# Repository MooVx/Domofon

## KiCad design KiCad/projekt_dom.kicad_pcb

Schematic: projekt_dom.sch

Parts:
C1: 33u; CP_Tantalum_Case-D_EIA-7343-31_Hand
C2, C3: 10u; C_0805_HandSoldering
C4: 470n; C_0805_HandSoldering
D1: IP_GOOD; LED_0805
D2: OPEN; LED_0805
J1: +12V; SolderWirePad_single_SMD_5x10mm
J2: RX; SolderWirePad_single_SMD_5x10mm
J3: OUT; SolderWirePad_single_SMD_5x10mm
J4: TX; SolderWirePad_single_SMD_5x10mm
J5: GND; SolderWirePad_single_SMD_5x10mm
Q1: NPN; SOT-23_Handsoldering
Q2: PNP; SOT-23_Handsoldering
R1, R2, R6: 1k; R_0805_HandSoldering
R3, R10: 10k; R_0805_HandSoldering
R4, R5: 100R; R_0805_HandSoldering
R7: 22k; R_0805_HandSoldering
R8: 33k; R_0805_HandSoldering
R9: 470R; R_0805_HandSoldering
U1: AMS1117-3.3; SOT-223
U2: ESP8266-12E/ESP-12E; XCVR_ESP8266-12E%2fESP-12E

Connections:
+3.3V: C1.1, C2.1, C3.1, C4.1, R1.2, R2.2, R3.2, U1.2, U2.8 (VCC)
+12V: J1.1, Q2.2, R7.2, U1.3
GND: C1.2, C2.2, C3.2, C4.2, D1.1, D2.1, J5.1, Q1.2, R10.1, U1.1, U1.4, U2.15 (GND)
unnamed: D1.2, R4.2
unnamed: D2.2, R5.1
unnamed: J2.1, U2.21 (RXD)
unnamed: J3.1, R9.1
unnamed: J4.1, U2.22 (TXD)
unnamed: Q1.1, R6.2
unnamed: Q1.3, R8.1
unnamed: Q2.1, R7.1, R8.2
unnamed: Q2.3, R9.2
unnamed: R1.1, U2.1 (RESET)
unnamed: R2.1, U2.3 (EN)
unnamed: R3.1, U2.18 (IO0)
unnamed: R4.1, U2.11 (IO9)
unnamed: R10.2, U2.16 (IO15)
OPEN: R5.2, R6.1, U2.6 (IO12)

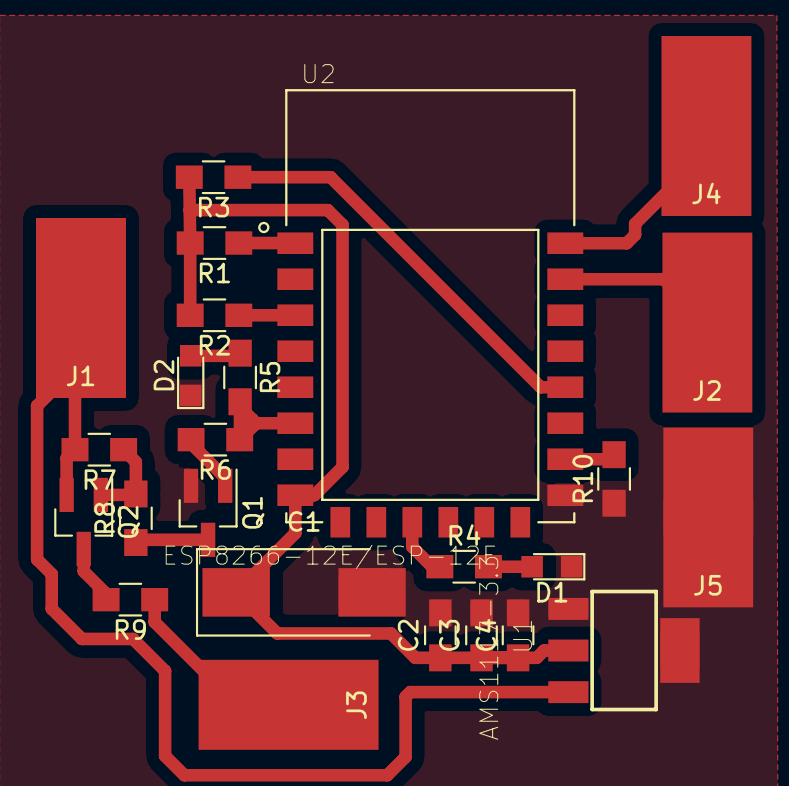
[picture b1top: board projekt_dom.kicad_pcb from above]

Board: 2 copper layers, 25 parts (0 on the bottom side), 18 nets.

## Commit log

2017-05-02 sprawko start
2017-05-02 sprwko cd
